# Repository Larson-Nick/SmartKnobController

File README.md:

# Smart Knob Controller

The Smart Knob Controller is an exploration of how brushless DC motors can breathe new life into one of the most ubiquitous input devices—the humble knob—by enabling dynamic, software-configurable feedback. The result is a clean, tactile, dual-degree-of-freedom controller that feels like multiple knobs in one: snappy detents, elastic spring force, or a completely free-spinning dial. The only limit is your creativity.

📘 [View the full Doxygen documentation here](https://larson-nick.github.io/SmartKnobController)

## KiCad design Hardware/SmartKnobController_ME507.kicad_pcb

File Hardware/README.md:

# Hardware

This folder contains all mechanical and electrical design files for the Smart Knob Controller, created using KiCAD v9.0 and SolidWorks 2024.

## Contents

- **Schematics (.sch)** – Complete circuit design
- **PCB Layout (.kicad_pcb)** – Board layout with mounting features
- **CAD** – For mechanical reference and rendering
- **DATASHEETS** - Incomplete list of datasheet PDFs for components
- **LIBRARIES** – Custom components and footprints
- **MANUFACTURING** - All manufacturing files used for production on JLCPCB.com
- **MEDIA** - Images and videos used for the webpage

Open the `.kicad_pro` or `.pro` file in KiCAD 7.0+ to explore the full project.

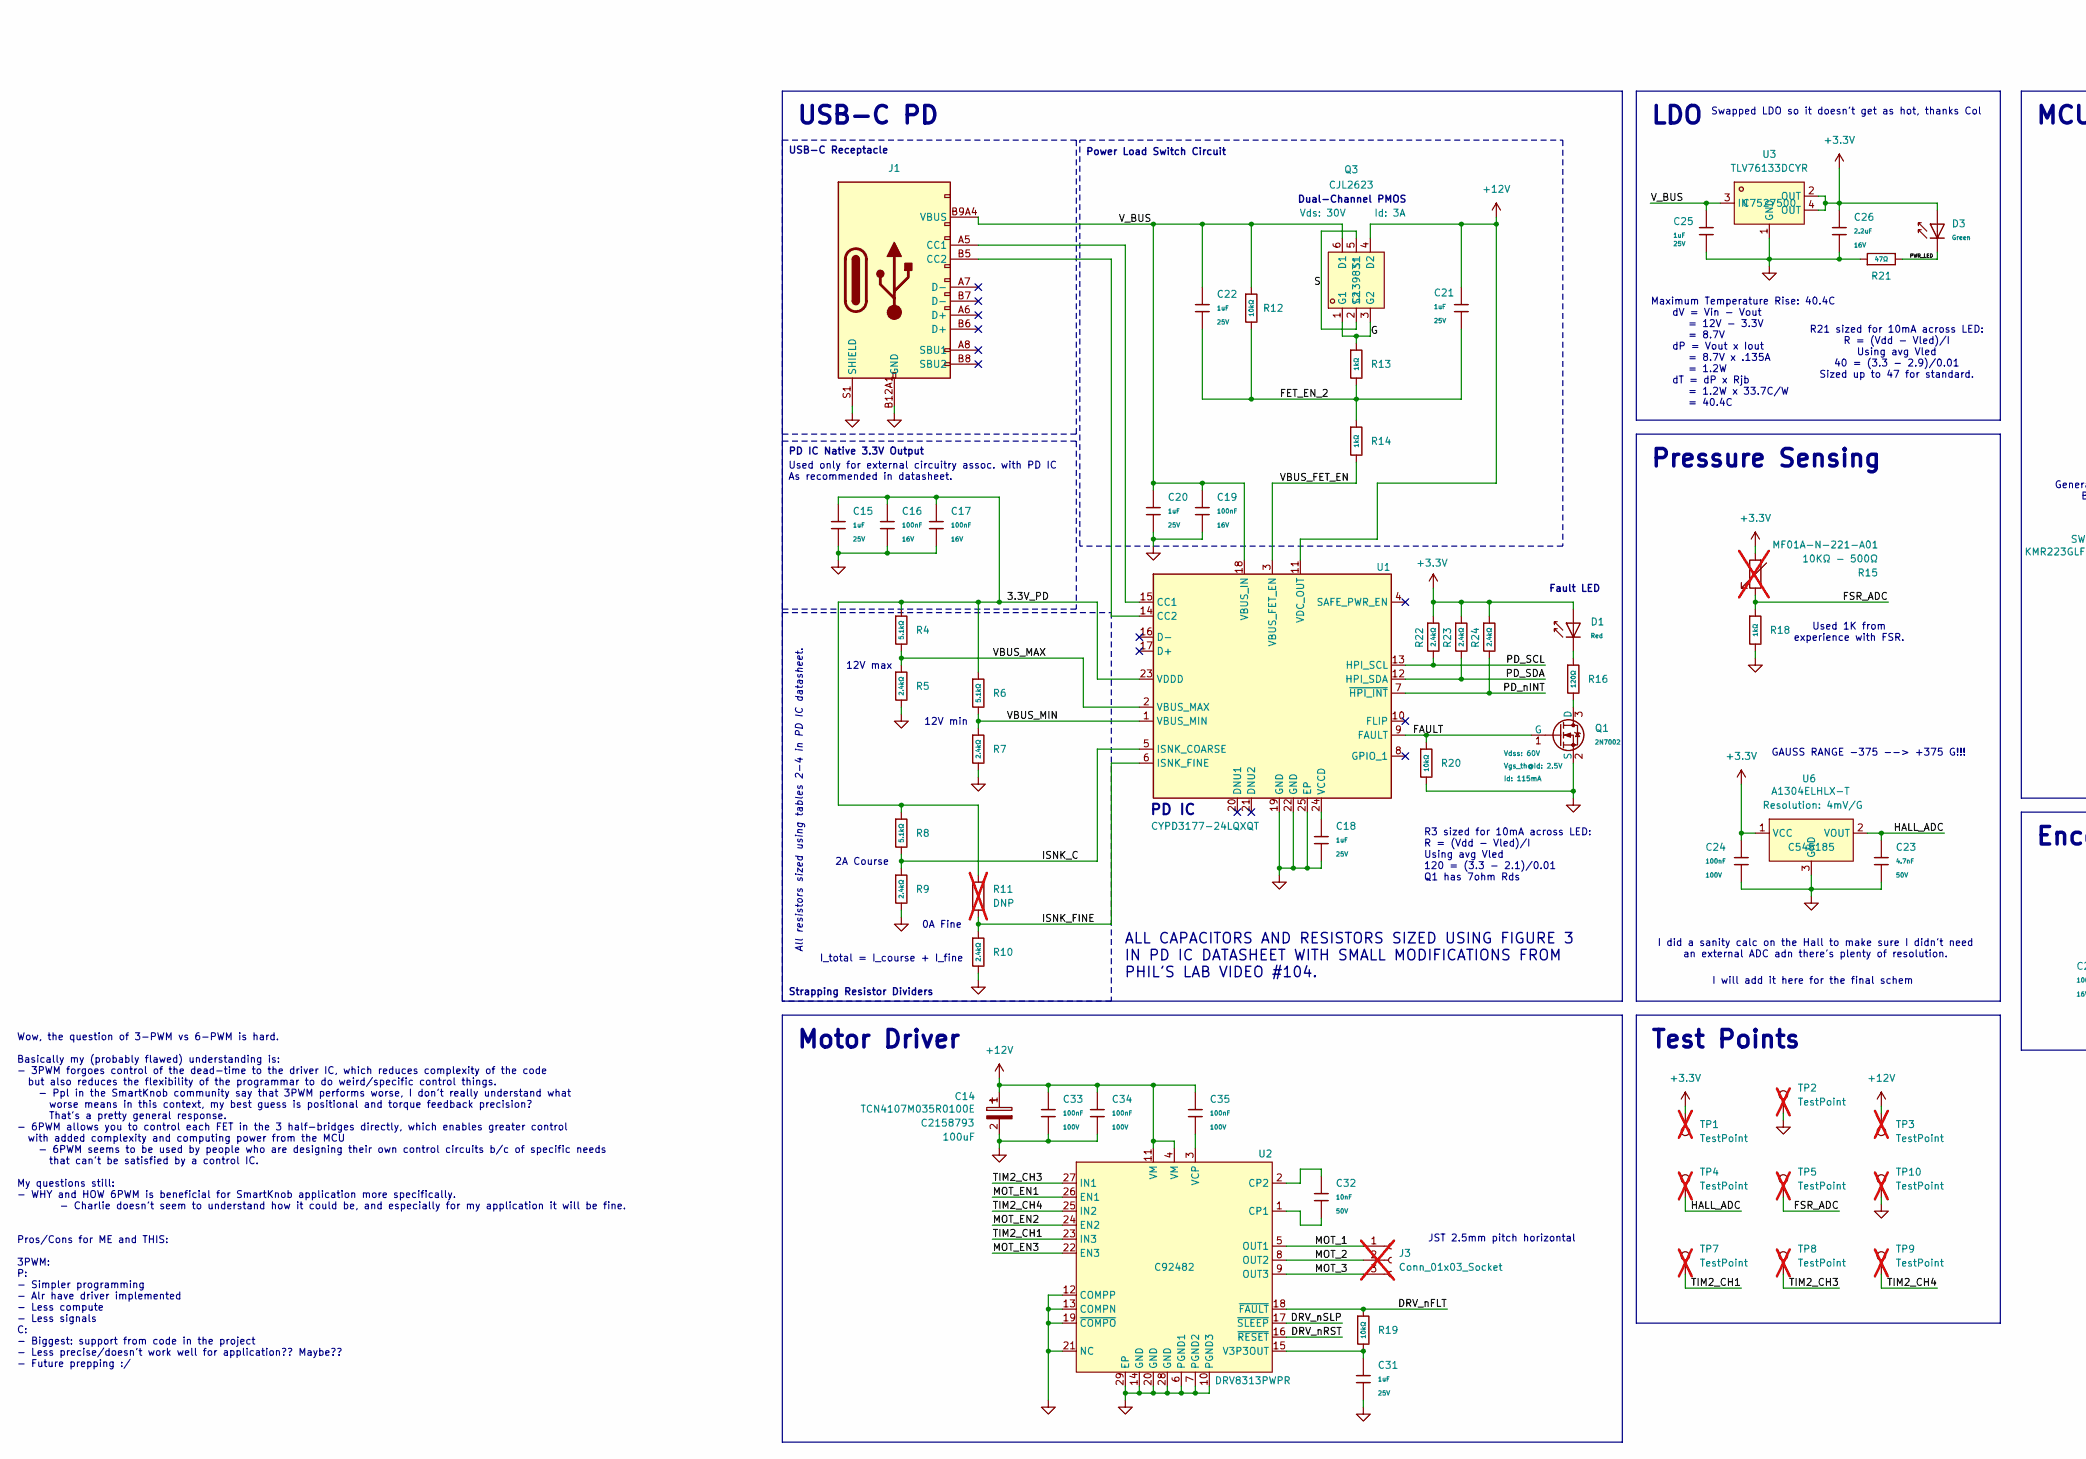
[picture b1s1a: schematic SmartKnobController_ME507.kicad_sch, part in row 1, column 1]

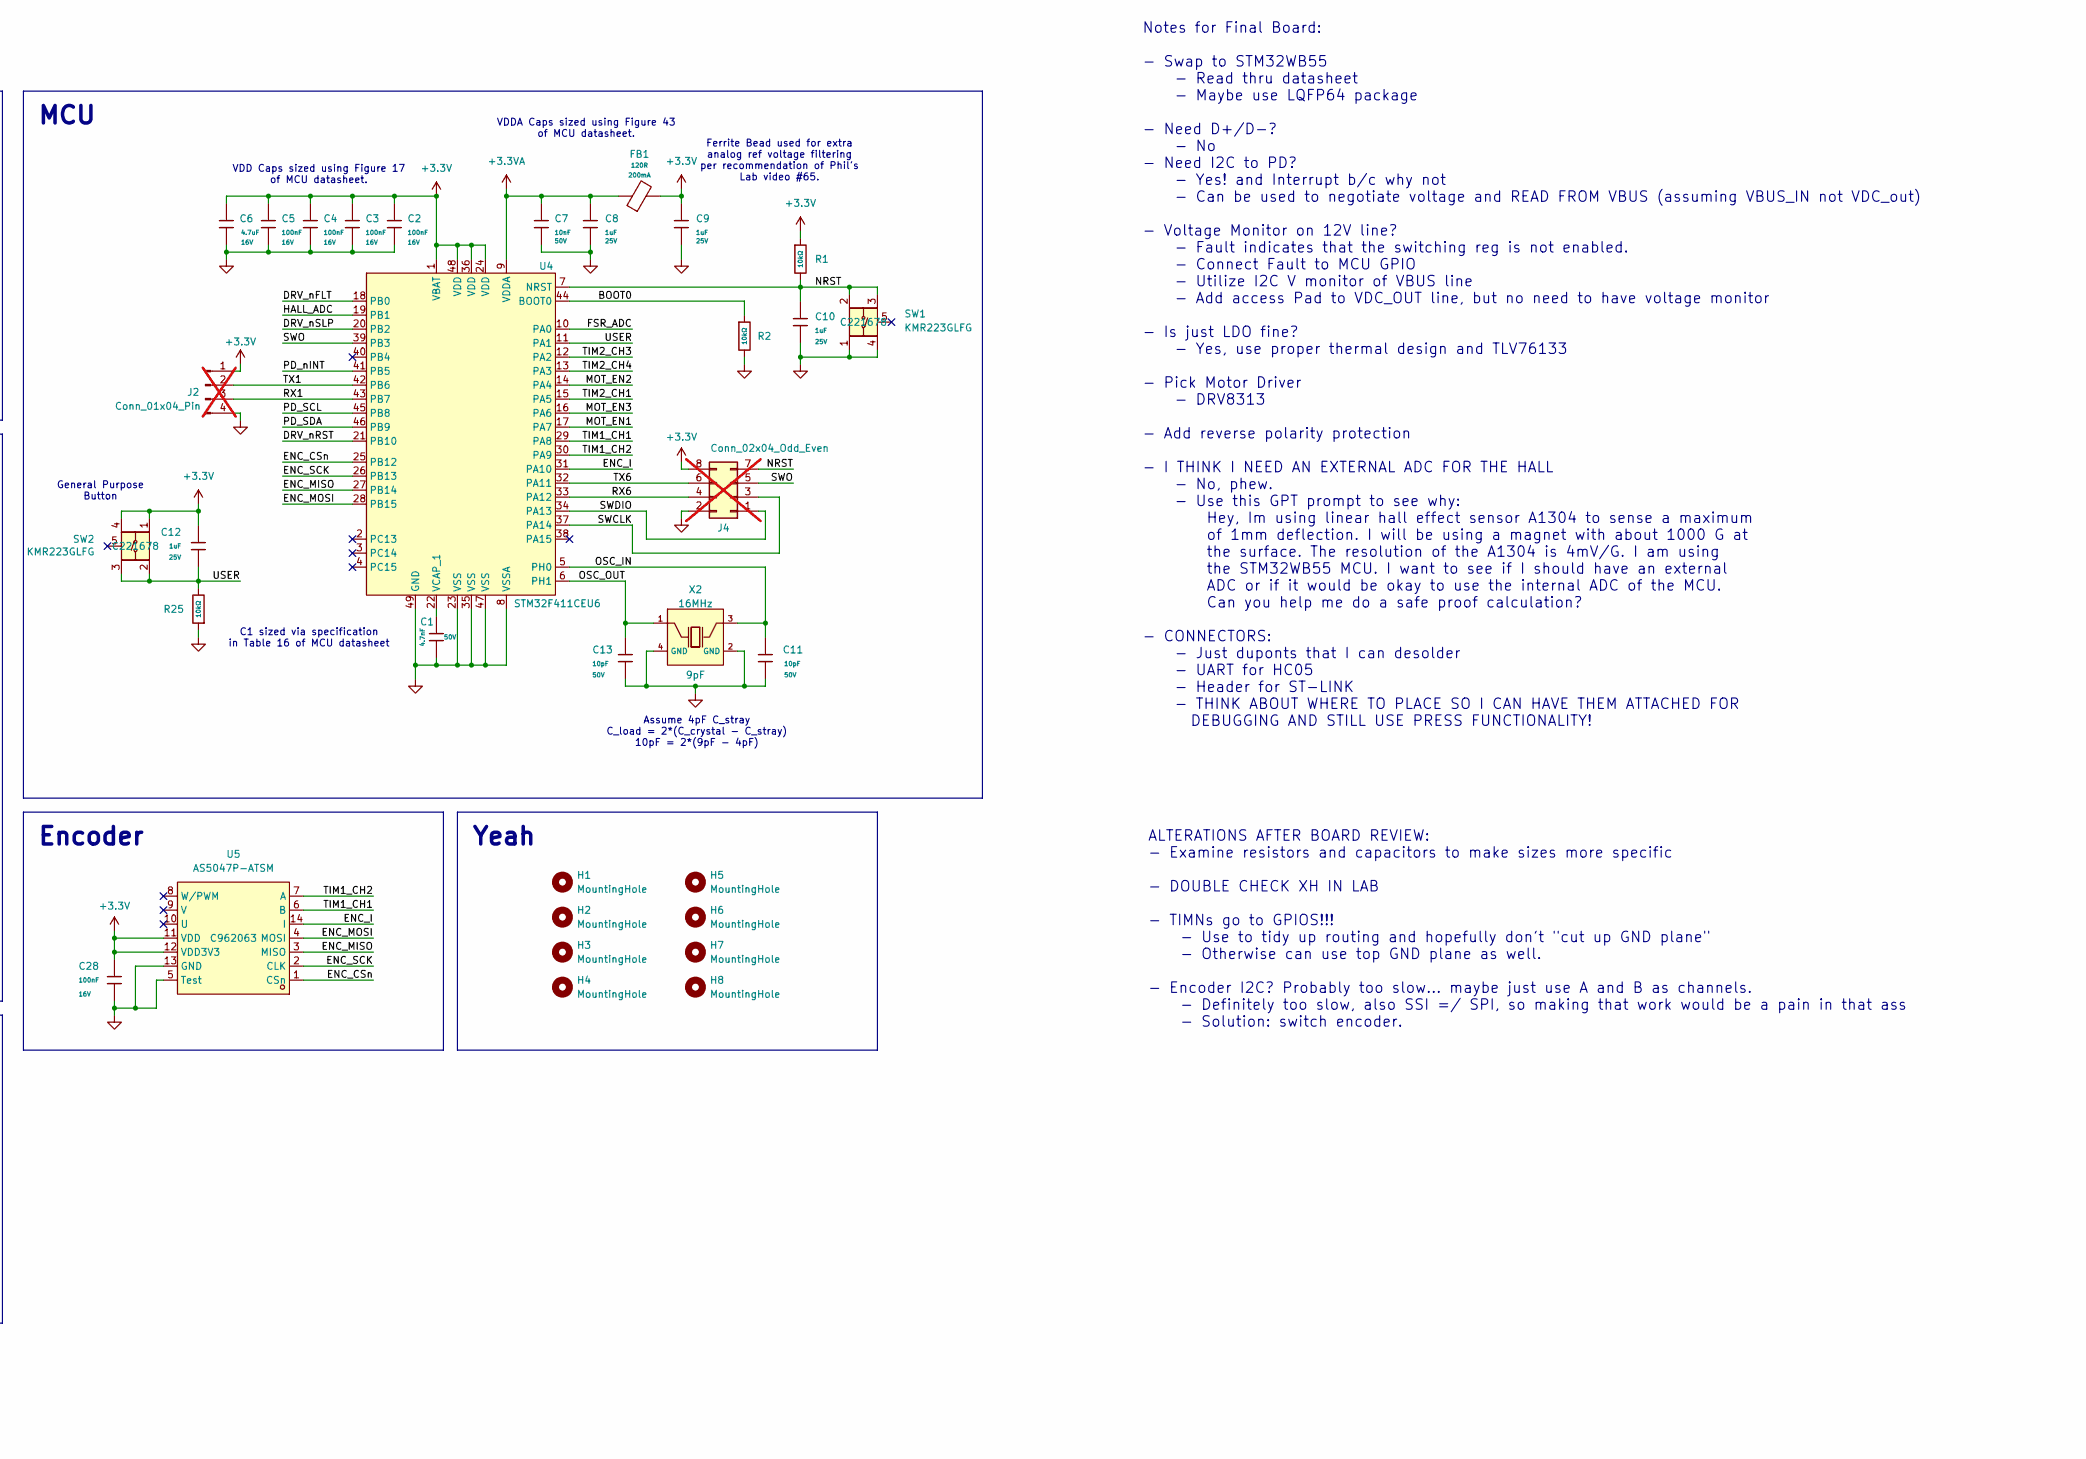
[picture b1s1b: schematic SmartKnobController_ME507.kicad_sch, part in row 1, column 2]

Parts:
C1: 4.7nF; C_0402; Voltage Rated 50V; Tolerance ±10%; Part 0402B472K500NT; LCSC C1538
C2, C3, C4, C5, C16, C17, C19, C28: 100nF; C_0402; Voltage Rated 16V; Tolerance ±10%; Part CL05B104KO5NNNC; LCSC C1525
C6: 4.7uF; C_0603; Voltage Rated 16V; Tolerance ±10%; Part CL10A475KO8NNNC; LCSC C19666
C7, C32: 10nF; C_0402; Voltage Rated 50V; Tolerance ±10%; Part CL05B103KB5NNNC; LCSC C15195
C8, C9, C10, C12, C15, C18, C20, C21, C22, C25, C31: 1uF; C_0402; Voltage Rated 25V; Tolerance ±10%; Part CL05A105KA5NQNC; LCSC C52923
C11, C13: 10pF; C_0402; Voltage Rated 50V; Tolerance ±5%; Part CL05C100JB5NNNC; LCSC C32949
C14: TCN4107M035R0100E; CAP-SMD_L7.3-W6.1_TCN4227M025R0100; LCSC Part C2158793
C23: 4.7nF; C_0805; Voltage Rated 50V; Tolerance ±10%; Part 0805B472K500NT; LCSC C1744
C24, C33, C34, C35: 100nF; C_0805; Voltage Rated 100V; Tolerance ±10%; Part CL21B104KCFNNNE; LCSC C28233
C26: 2.2uF; C_0603; Voltage Rated 16V; Tolerance ±10%; Part CL10A225KO8NNNC; LCSC C23630
D1: Red; D_0603; Part KT-0603R; LCSC C2286
D3: Green; D_0805; Part KT-0805G; LCSC C2297
FB1: 120R; FB_0603; Current Rating 200mA; Tolerance ±25%; Part GZ1608D601TF; LCSC C1002
H1, H2, H3, H4: MountingHole; MountingHole_2.7mm_M2.5
H5, H6, H7, H8: MountingHole; MountingHole_3.2mm_M3
J1: Connector, USB-TYPE-C-16P; TYPE-C-SMD_HX-TYPE-C-16PIN; LCSC C2927039
J2: Conn_01x04_Pin; PinHeader_1x04_P2.54mm_Horizontal; not fitted
J3: Conn_01x03_Socket; JST_XH_S3B-XH-A_1x03_P2.50mm_Horizontal; not fitted
J4: Conn_02x04_Odd_Even; PinHeader_2x04_P2.54mm_Vertical; not fitted
Q1: 2N7002; Q_SOT-23; Part 2N7002; LCSC C8545
Q3: CJL2623; SOT-23-6_L2.9-W1.6-P0.95-LS2.8-BR; LCSC Part C139831
R1, R2, R12, R19, R25: 10kΩ; R_0402; Overload Voltage (Max) 50V; Tolerance ±1%; Part 0402WGF1002TCE; LCSC C25744
R4, R6, R8: 5.1kΩ; R_0603; Overload Voltage (Max) 75V; Tolerance ±1%; Part 0603WAF5101T5E; LCSC C23186
R5, R7, R9, R10: 2.4kΩ; R_0603; Overload Voltage (Max) 75V; Tolerance ±1%; Part 0603WAF2401T5E; LCSC C22940
R11: DNP; R_0603; not fitted
R13, R14: 1kΩ; R_0402; Overload Voltage (Max) 50V; Tolerance ±1%; Part 0402WGF1001TCE; LCSC C11702
R15: 10KΩ - 500Ω; MF01A-N-221-A05; not fitted
R16: 120Ω; R_0603; Overload Voltage (Max) 75V; Tolerance ±1%; Part 0603WAF1200T5E; LCSC C22787
R18: 1kΩ; R_0603; Overload Voltage (Max) 75V; Tolerance ±1%; Part 0603WAF1001T5E; LCSC C21190
R20: 10kΩ; R_0603; Overload Voltage (Max) 75V; Tolerance ±1%; Part 0603WAF1002T5E; LCSC C25804
R21: 47Ω; R_0402; Overload Voltage (Max) 50V; Tolerance ±1%; Part 0402WGF470JTCE; LCSC C25118
R22, R23, R24: 2.4kΩ; R_0402; Overload Voltage (Max) 50V; Tolerance ±1%; Part 0402WGF2401TCE; LCSC C25882
SW1, SW2: KMR223GLFG; SW-SMD_5P-L4.2-W2.8-P1.60-LS4.6-TR; LCSC Part C221678
TP1, TP2, TP3, TP4, TP5, TP7, TP8, TP9, TP10: TestPoint; Test Point; not fitted
U1: CYPD3177-24LQXQT; QFN24_CYPD3177-24LQXQT_INF; LCSC C5904158
U2: DRV8313PWPR; HTSSOP-28_L9.8-W4.5-P0.65-LS6.6-BL-EP; LCSC Part C92482
U3: TLV76133DCYR; SOT-223-4_L6.5-W3.5-P2.30-LS7.0-TR; LCSC Part C7527500
U4: STM32F411CEU6; LCSC C60420
U5: AS5047P-ATSM; TSSOP-14_L5.0-W4.4-P0.65-LS6.4-BL; LCSC Part C962063
U6: A1304ELHLX-T; SOT-23-3_L3.0-W1.9-P0.95-LS2.9-BL; LCSC Part C545185
X2: X322516MLB4SI; OSC-SMD_4P-L3.2-W2.5-BL; Frequency Tolerance ±10ppm; Part X322516MLB4SI; LCSC C13738

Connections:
+3.3V: C2.1, C3.1, C4.1, C5.1, C6.1, C9.1, C12.2, C24.1, C26.1, C28.2, D1.2, D3.2, FB1.2, J2.1, J4.8, R1.1, R15.2, R22.1, R23.1, R24.1, SW2.1, SW2.4, TP1.1, U3.2 (OUT), U3.4 (OUT), U4.1 (VBAT), U4.24 (VDD), U4.36 (VDD), U4.48 (VDD), U5.11 (VDD), U5.12 (VDD3V3), U6.1 (VCC)
+3.3VA: C7.1, C8.1, FB1.1, U4.9 (VDDA)
+12V: C14.1, C21.1, C33.1, C34.1, C35.1, Q3.4 (D2), TP3.1, U1.11 (VDC_OUT), U2.4 (VM), U2.11 (VM)
/3.3V_PD: C15.1, C16.1, C17.1, R4.1, R6.1, R8.1, R11.1, U1.23 (VDDD)
/BOOT0: R2.1, U4.44 (BOOT0)
/DRV_nFLT: R19.1, U2.18 (~FAULT), U4.18 (PB0)
/DRV_nRST: U2.16 (~RESET), U4.21 (PB10)
/DRV_nSLP: U2.17 (~SLEEP), U4.20 (PB2)
/ENC_CSn: U4.25 (PB12), U5.1 (CSn)
/ENC_I: U4.31 (PA10), U5.14 (I)
/ENC_MISO: U4.27 (PB14), U5.3 (MISO)
/ENC_MOSI: U4.28 (PB15), U5.4 (MOSI)
/ENC_SCK: U4.26 (PB13), U5.2 (CLK)
/FAULT: Q1.1 (G), R20.1, U1.9 (FAULT)
/FET_EN_2: C21.2, C22.2, R12.2, R13.2, R14.1
/FSR_ADC: R15.1, R18.1, TP5.1, U4.10 (PA0)
/G: Q3.1 (G1), Q3.3 (G2), R13.1
/HALL_ADC: C23.1, TP4.1, U4.19 (PB1), U6.2 (VOUT)
/ISNK_C: R8.2, R9.1, U1.5 (ISNK_COARSE)
/ISNK_FINE: R10.1, R11.2, U1.6 (ISNK_FINE)
/MOT_1: J3.1, U2.5 (OUT1)
/MOT_2: J3.2, U2.8 (OUT2)
/MOT_3: J3.3, U2.9 (OUT3)
/MOT_EN1: U2.26 (EN1), U4.17 (PA7)
/MOT_EN2: U2.24 (EN2), U4.14 (PA4)
/MOT_EN3: U2.22 (EN3), U4.16 (PA6)
/NRST: C10.1, J4.7, R1.2, SW1.2, SW1.3, U4.7 (NRST)
/OSC_IN: C11.1, U4.5 (PH0), X2.3 (OSC)
/OSC_OUT: C13.1, U4.6 (PH1), X2.1 (OSC)
/PD_SCL: R22.2, U1.13 (HPI_SCL), U4.45 (PB8)
/PD_SDA: R23.2, U1.12 (HPI_SDA), U4.46 (PB9)
/PD_nINT: R24.2, U1.7 (~HPI_INT), U4.41 (PB5)
/PWR_LED: D3.1, R21.2
/RX1: J2.3, U4.43 (PB7)
/RX6: J4.4, U4.33 (PA12)
/S: Q3.2 (S2), Q3.5 (S1)
/SWCLK: J4.3, U4.37 (PA14)
/SWDIO: J4.1, U4.34 (PA13)
/SWO: J4.5, U4.39 (PB3)
/TIM1_CH1: U4.29 (PA8), U5.6 (B)
/TIM1_CH2: U4.30 (PA9), U5.7 (A)
/TIM2_CH1: TP7.1, U2.23 (IN3), U4.15 (PA5)
/TIM2_CH3: TP8.1, U2.27 (IN1), U4.12 (PA2)
/TIM2_CH4: TP9.1, U2.25 (IN2), U4.13 (PA3)
/TX1: J2.2, U4.42 (PB6)
/TX6: J4.6, U4.32 (PA11)
/USER: C12.1, R25.2, SW2.2, SW2.3, U4.11 (PA1)
/VBUS_FET_EN: R14.2, U1.3 (VBUS_FET_EN)
/VBUS_MAX: R4.2, R5.1, U1.2 (VBUS_MAX)
/VBUS_MIN: R6.2, R7.1, U1.1 (VBUS_MIN)
/V_BUS: C19.1, C20.1, C22.1, C25.1, J1.A9B4 (VBUS), J1.B9A4 (VBUS), Q3.6 (D1), R12.1, U1.18 (VBUS_IN), U3.3 (IN)
GND: C1.2, C2.2, C3.2, C4.2, C5.2, C6.2, C7.2, C8.2, C9.2, C10.2, C11.2, C13.2, C14.2, C15.2, C16.2, C17.2, C18.2, C19.2, C20.2, C23.2, C24.2, C25.2, C26.2, C28.1, C31.2, C33.2, C34.2, J1.A12B1 (GND), J1.B12A1 (GND), J1.S1 (SHIELD), J2.4, J4.2, Q1.2 (S), R2.2, R5.2, R7.2, R9.2, R10.2, R18.2, R20.2, R21.1, R25.1, SW1.1, SW1.4, TP2.1, TP10.1, U1.19 (GND), U1.22 (GND), U1.25 (EP), U2.6 (PGND1), U2.7 (PGND2), U2.10 (PGND3), U2.12 (COMPP), U2.13 (COMPN), U2.14 (GND), U2.19 (~COMPO), U2.20 (GND), U2.21 (NC), U2.28 (GND), U2.29 (EP), U3.1 (GND), U4.8 (VSSA), U4.23 (VSS), U4.35 (VSS), U4.47 (VSS), U4.49 (GND), U5.5 (Test), U5.13 (GND), U6.3 (GND), X2.2 (GND), X2.4 (GND)
unnamed: D1.1, R16.1
unnamed: J1.A5 (CC1), U1.15 (CC1)
unnamed: J1.B5 (CC2), U1.14 (CC2)
unnamed: Q1.3 (D), R16.2
unnamed: C18.1, U1.24 (VCCD)
unnamed: C32.2, U2.1 (CP1)
unnamed: C32.1, U2.2 (CP2)
unnamed: C31.1, R19.2, U2.15 (V3P3OUT)
unnamed: C35.2, U2.3 (VCP)
unnamed: C1.1, U4.22 (VCAP_1)

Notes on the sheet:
Dual-Channel PMOS
R3 sized for 10mA across LED: R = (Vdd - Vled)/I Using avg Vled 120 = (3.3 - 2.1)/0.01 Q1 has 7ohm Rds
Used only for external circuitry assoc. with PD IC As recommended in datasheet.
Used 1K from experience with FSR.
Fault LED
Maximum Temperature Rise: 40.4C dV = Vin - Vout = 12V - 3.3V = 8.7V dP = Vout x Iout = 8.7V x .135A = 1.2W dT = dP x Rjb = 1.2W x 33.7C/W = 40.4C
VDDA Caps sized using Figure 43 of MCU datasheet.
R21 sized for 10mA across LED: R = (Vdd - Vled)/I Using avg Vled 40 = (3.3 - 2.9)/0.01 Sized up to 47 for standard.
12V min
2A Course
C1 sized via specification in Table 16 of MCU datasheet
GAUSS RANGE -375 --> +375 G!!!
0A Fine
ALTERATIONS AFTER BOARD REVIEW: - Examine resistors and capacitors to make sizes more specific - DOUBLE CHECK XH IN LAB - TIMNs go to GPIOS!!! - Use to tidy up routing and hopefully don't "cut up GND plane" - Otherwise can use top GND plane as well. - Encoder I2C? Probably too slow... maybe just us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
PD IC
VDD Caps sized using Figure 17 of MCU datasheet.
Power Load Switch Circuit
General Purpose Button
JST 2.5mm pitch horizontal
I did a sanity calc on the Hall to make sure I didn't need an external ADC adn there's plenty of resolution.
Notes for Final Board: - Swap to STM32WB55 - Read thru datasheet - Maybe use LQFP64 package - Need D+/D-? - No - Need I2C to PD? - Yes! and Interrupt b/c why not - Can be used to negotiate voltage and READ FROM VBUS (assuming VBUS_IN not VDC_out) - Voltage Monitor on 12V line? - Fault indicates tha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
Swapped LDO so it doesn't get as hot, thanks Col
Wow, the question of 3-PWM vs 6-PWM is hard. Basically my (probably flawed) understanding is: - 3PWM forgoes control of the dead-time to the driver IC, which reduces complexity of the code but also reduces the flexibility of the programmar to do weird/specific control things. - Ppl in the SmartKnob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
Assume 4pF C_stray C_load = 2*(C_crystal - C_stray) 10pF = 2*(9pF - 4pF)
I will add it here for the final schem
I_total = I_course + I_fine
12V max
All resistors sized using tables 2-4 in PD IC datasheet.
ALL CAPACITORS AND RESISTORS SIZED USING FIGURE 3 IN PD IC DATASHEET WITH SMALL MODIFICATIONS FROM PHIL'S LAB VIDEO #104.
Ferrite Bead used for extra analog ref voltage filtering per recommendation of Phil's Lab video #65.
Motor Driver
LDO
Pressure Sensing
Encoder
PD IC Native 3.3V Output
Strapping Resistor Dividers
Test Points
Yeah
USB-C Receptacle
USB-C PD

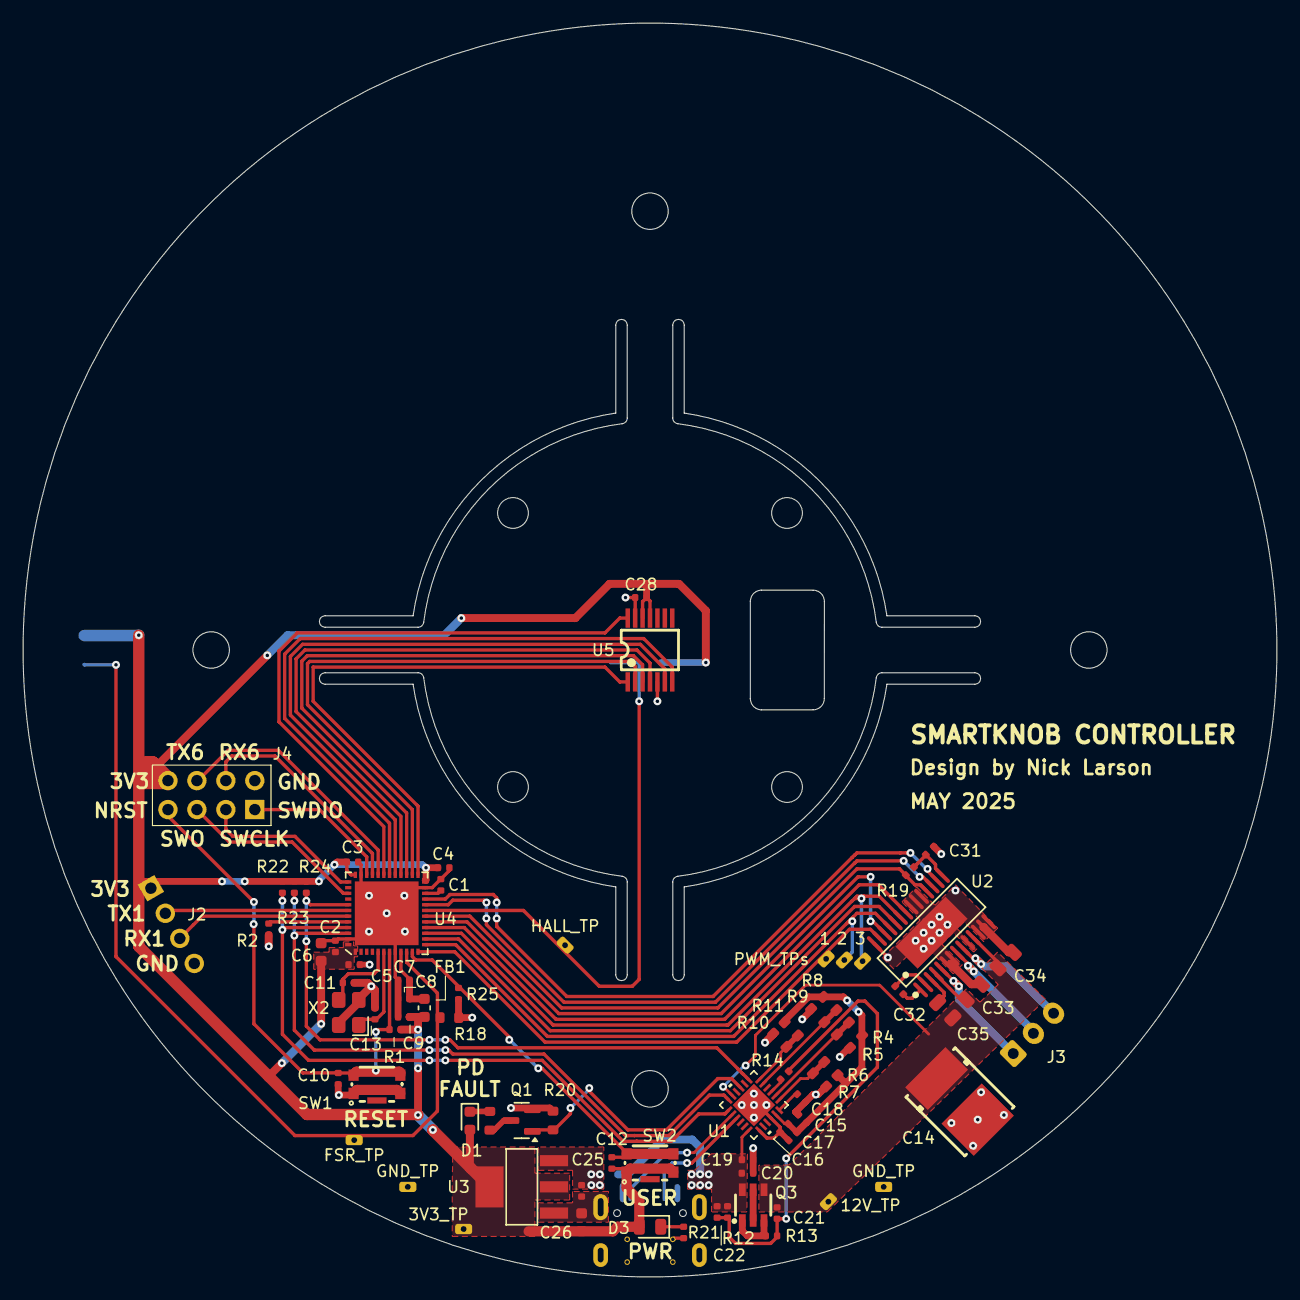
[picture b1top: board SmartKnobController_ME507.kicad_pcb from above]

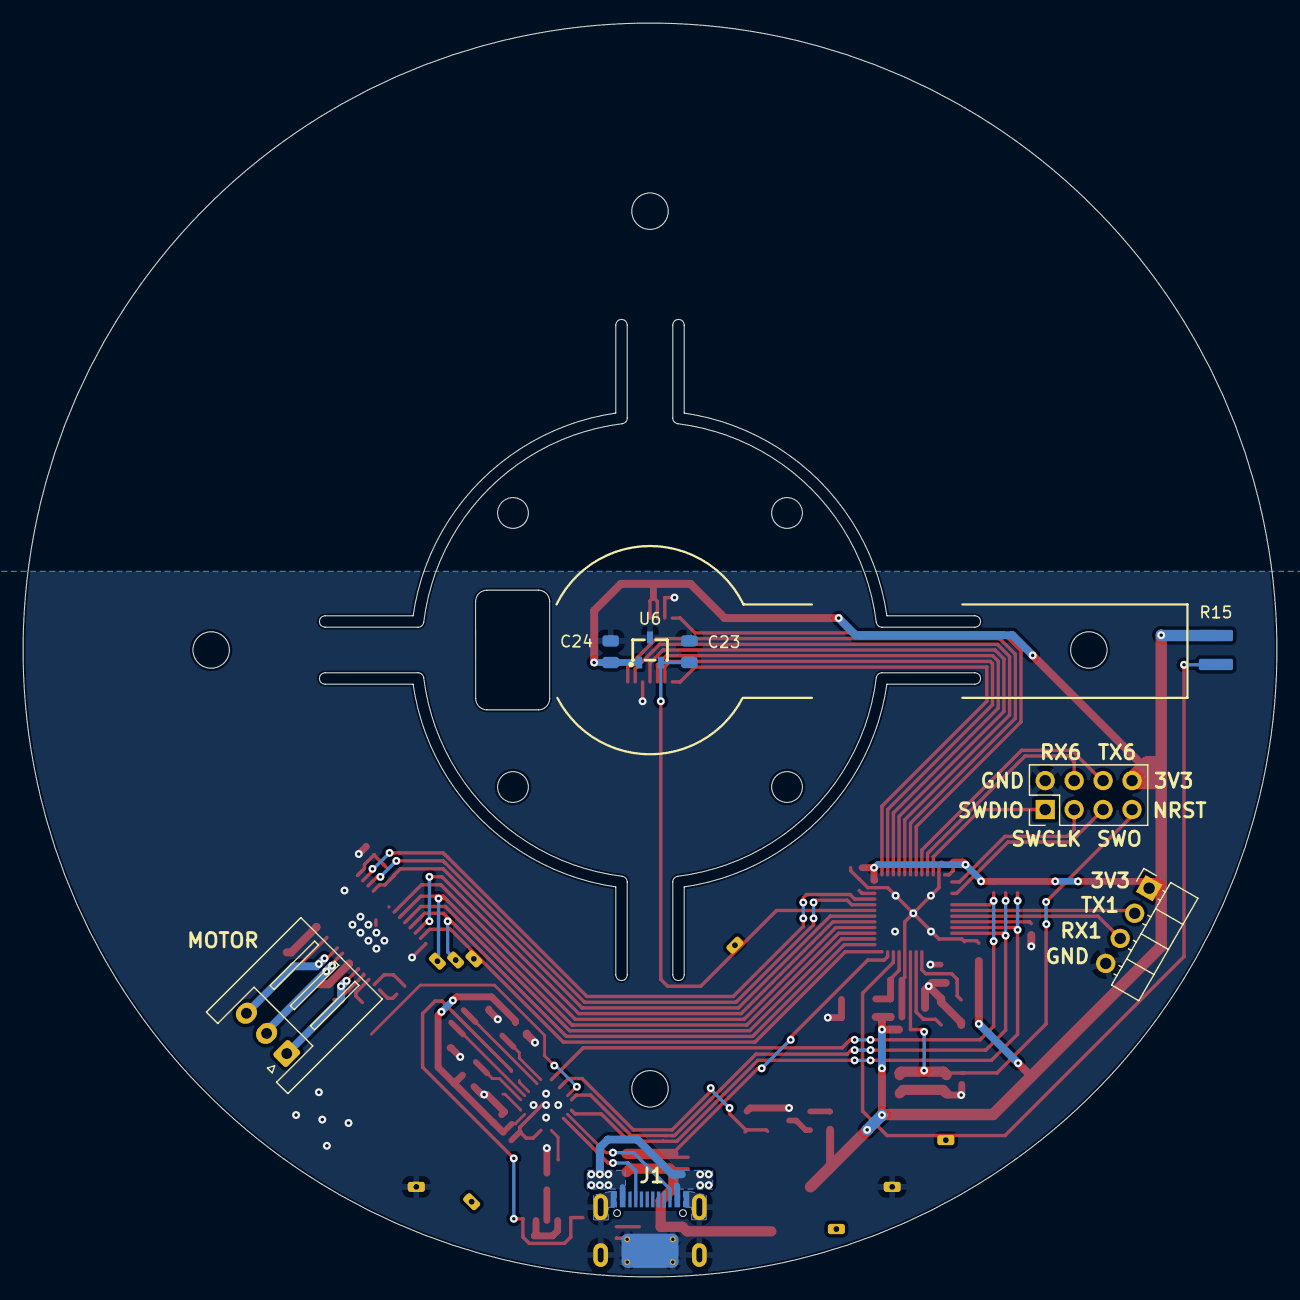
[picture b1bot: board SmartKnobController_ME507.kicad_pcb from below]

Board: 2 copper layers, 110.0 x 110.0 mm, 90 parts (8 on the bottom side), 62 nets.

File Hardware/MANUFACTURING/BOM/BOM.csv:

"Reference","Value","Footprint","Description","Qty","LCSC","DNP"
"Q3","CJL2623","0_TRANSISTOR:SOT-23-6_L2.9-W1.6-P0.95-LS2.8-BR","","1","C139831",""
"U5","AS5047P-ATSM","0_SENSOR:TSSOP-14_L5.0-W4.4-P0.65-LS6.4-BL","","1","C962063",""
"D1","Red","PCM_JLCPCB:D_0603","-40°C~+85°C Red 0603 LED Indication - Discrete ROHS","1","C2286",""
"R20","10kΩ","PCM_JLCPCB:R_0603","100mW Thick Film Resistors 75V ±100ppm/°C ±1% 10kΩ 0603 Chip Resistor - Surface Mount ROHS","1","C25804",""
"R16","120Ω","PCM_JLCPCB:R_0603","100mW Thick Film Resistors 75V ±100ppm/°C ±1% 120Ω 0603 Chip Resistor - Surface Mount ROHS","1","C22787",""
"R18","1kΩ","PCM_JLCPCB:R_0603","100mW Thick Film Resistors 75V ±100ppm/°C ±1% 1kΩ 0603 Chip Resistor - Surface Mount ROHS","1","C21190",""
"R5,R7,R9,R10","2.4kΩ","PCM_JLCPCB:R_0603","100mW Thick Film Resistors 75V ±100ppm/°C ±1% 2.4kΩ 0603 Chip Resistor - Surface Mount ROHS","4","C22940",""
"R4,R6,R8","5.1kΩ","PCM_JLCPCB:R_0603","100mW Thick Film Resistors 75V ±100ppm/°C ±1% 5.1kΩ 0603 Chip Resistor - Surface Mount ROHS","3","C23186",""
"C14","TCN4107M035R0100E","0_CAPACITOR:CAP-SMD_L7.3-W6.1_TCN4227M025R0100","100uF 35V 100mΩ@100kHz ±20% Tantalum Capacitors ROHS","1","C2158793",""
"C24,C33,C34,C35","100nF","PCM_JLCPCB:C_0805","100V 100nF X7R ±10% 0805 Multilayer Ceramic Capacitors MLCC - SMD/SMT ROHS","4","C28233",""
"X2","X322516MLB4SI","PCM_JLCPCB:OSC-SMD_4P-L3.2-W2.5-BL","16MHz Surface Mount Crystal 9pF ±10ppm ±20ppm SMD3225-4P Crystals ROHS","1","C13738",""
"C2,C3,C4,C5,C16,C17,C19,C28","100nF","PCM_JLCPCB:C_0402","16V 100nF X7R ±10% 0402 Multilayer Ceramic Capacitors MLCC - SMD/SMT ROHS","8","C1525",""
"C26","2.2uF","PCM_JLCPCB:C_0603","16V 2.2uF X5R ±10% 0603 Multilayer Ceramic Capacitors MLCC - SMD/SMT ROHS","1","C23630",""
"C6","4.7uF","PCM_JLCPCB:C_0603","16V 4.7uF X5R ±10% 0603 Multilayer Ceramic Capacitors MLCC - SMD/SMT ROHS","1","C19666",""
"U3","TLV76133DCYR","0_PWR:SOT-223-4_L6.5-W3.5-P2.30-LS7.0-TR","1A Fixed 3.3V Positive electrode 16V SOT-223 Voltage Regulators - Linear, Low Drop Out (LDO) Regulators ROHS","1","C7527500",""
"C8,C9,C10,C12,C15,C18,C20,C21,C22,C25,C31","1uF","PCM_JLCPCB:C_0402","25V 1uF X5R ±10% 0402 Multilayer Ceramic Capacitors MLCC - SMD/SMT ROHS","11","C52923",""
"J1","Connector, USB-TYPE-C-16P","PCM_JLCPCB:TYPE-C-SMD_HX-TYPE-C-16PIN","3A 1 Horizontal attachment 16P Female -25℃~+85℃ Type-C SMD USB Connectors ROHS","1","C2927039",""
"FB1","120R","PCM_JLCPCB:FB_0603","450mΩ ±25% 600Ω@100MHz 0603 Ferrite Beads ROHS","1","C1002",""
"C7,C32","10nF","PCM_JLCPCB:C_0402","50V 10nF X7R ±10% 0402 Multilayer Ceramic Capacitors MLCC - SMD/SMT ROHS","2","C15195",""
"C11,C13","10pF","PCM_JLCPCB:C_0402","50V 10pF C0G ±5% 0402 Multilayer Ceramic Capacitors MLCC - SMD/SMT ROHS","2","C32949",""
"C1","4.7nF","PCM_JLCPCB:C_0402","50V 4.7nF X7R ±10% 0402 Multilayer Ceramic Capacitors MLCC - SMD/SMT ROHS","1","C1538",""
"C23","4.7nF","PCM_JLCPCB:C_0805","50V 4.7nF X7R ±10% 0805 Multilayer Ceramic Capacitors MLCC - SMD/SMT ROHS","1","C1744",""
"Q1","2N7002","PCM_JLCPCB:Q_SOT-23","60V 115mA 200mW 7.5Ω@10V,500mA 2.5V@250uA 1 N-Channel SOT-23 MOSFETs ROHS","1","C8545",""
"R21","47Ω","PCM_JLCPCB:R_0402","62.5mW Thick Film Resistors 50V ±1% ±200ppm/°C 47Ω 0402 Chip Resistor - Surface Mount ROHS","1","C25118",""
"R1,R2,R12,R19,R25","10kΩ","PCM_JLCPCB:R_0402","62.5mW Thick Film Resistors 50V ±100ppm/°C ±1% 10kΩ 0402 Chip Resistor - Surface Mount ROHS","5","C25744",""
"R13,R14","1kΩ","PCM_JLCPCB:R_0402","62.5mW Thick Film Resistors 50V ±100ppm/°C ±1% 1kΩ 0402 Chip Resistor - Surface Mount ROHS","2","C11702",""
"R22,R23,R24","2.4kΩ","PCM_JLCPCB:R_0402","62.5mW Thick Film Resistors 50V ±100ppm/°C ±1% 2.4kΩ 0402 Chip Resistor - Surface Mount ROHS","3","C25882",""
"U4","STM32F411CEU6","0_MCU:STM32F411CEU6","ARM-M4 100MHz UFQFPN-48(7x7) Microcontrollers (MCU/MPU/SOC) ROHS","1","C60420",""
"D3","Green","PCM_JLCPCB:D_0805","Emerald 0805 LED Indication - Discrete ROHS","1","C2297",""
"U2","DRV8313PWPR","0_DRIVER:HTSSOP-28_L9.8-W4.5-P0.65-LS6.6-BL-EP","HTSSOP-28-EP-4.5mm Brushless DC (BLDC) Motor Driver ROHS","1","C92482",""
"SW1,SW2","KMR223GLFG","0_MISC:SW-SMD_5P-L4.2-W2.8-P1.60-LS4.6-TR","Round Button 10mA Standing paste SPST - normally open 32V 200gf SMD Tactile Switches ROHS","2","C221678",""
"U6","A1304ELHLX-T","0_SENSOR:SOT-23-3_L3.0-W1.9-P0.95-LS2.9-BL","SOT-23W Linear Hall Sensors ROHS","1","C545185",""
"U1","CYPD3177-24LQXQT","0_PWR:QFN24_CYPD3177-24LQXQT_INF","Stand-alone USB PD controller (with sink Auto-run mode), QFN-24","1","C5904158",""

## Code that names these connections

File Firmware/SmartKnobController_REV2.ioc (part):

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Mcu.Name=STM32F411C(C-E)Ux
Mcu.Package=UFQFPN48
Mcu.UserName=STM32F411CEUx
PA1.GPIOParameters=GPIO_ModeDefaultEXTI
PA1.GPIO_ModeDefaultEXTI=GPIO_MODE_IT_RISING_FALLING
PA1.Signal=GPXTI1
PA11.Mode=Asynchronous
PA11.Signal=USART6_TX
PA12.Mode=Asynchronous
PA12.Signal=USART6_RX
PA13.Mode=Trace_Asynchronous_SW
PA13.Signal=SYS_JTMS-SWDIO
PA14.Mode=Trace_Asynchronous_SW
PA14.Signal=SYS_JTCK-SWCLK
PA2.Signal=S_TIM2_CH3
PA3.Signal=S_TIM2_CH4
PA4.GPIOParameters=PinState
PA4.PinState=GPIO_PIN_RESET
PA4.Signal=GPIO_Output
PA5.Signal=S_TIM2_CH1_ETR
PA6.GPIOParameters=PinState
PA6.PinState=GPIO_PIN_RESET
PA6.Signal=GPIO_Output
PA7.GPIOParameters=PinState
PA7.PinState=GPIO_PIN_RESET
PA7.Signal=GPIO_Output
PB1.Signal=ADCx_IN9
PB10.GPIOParameters=PinState
PB10.PinState=GPIO_PIN_SET
PB10.Signal=GPIO_Output
PB12.Signal=GPIO_Output
PB13.Mode=Full_Duplex_Master
PB13.Signal=SPI2_SCK
PB14.Mode=Full_Duplex_Master
PB14.Signal=SPI2_MISO
PB15.Mode=Full_Duplex_Master
PB15.Signal=SPI2_MOSI
PB2.GPIOParameters=PinState
PB2.PinState=GPIO_PIN_SET
PB2.Signal=GPIO_Output
PB3.Mode=Trace_Asynchronous_SW
PB3.Signal=SYS_JTDO-SWO
PB6.Mode=Asynchronous
PB6.Signal=USART1_TX
PB7.Mode=Asynchronous
PB7.Signal=USART1_RX
PH0\ -\ OSC_IN.Mode=HSE-External-Oscillator
PH0\ -\ OSC_IN.Signal=RCC_OSC_IN
PH1\ -\ OSC_OUT.Mode=HSE-External-Oscillator
PH1\ -\ OSC_OUT.Signal=RCC_OSC_OUT
RCC.HSE_VALUE=16000000
RCC.SYSCLKFreq_VALUE=72000000
RCC.SYSCLKSource=RCC_SYSCLKSOURCE_PLLCLK
board=custom

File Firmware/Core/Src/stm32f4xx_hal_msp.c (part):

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void HAL_MspInit(void)
{

  /* USER CODE BEGIN MspInit 0 */

  /* USER CODE END MspInit 0 */

  __HAL_RCC_SYSCFG_CLK_ENABLE();
  __HAL_RCC_PWR_CLK_ENABLE();

  /* System interrupt init*/

  /* USER CODE BEGIN MspInit 1 */

  /* USER CODE END MspInit 1 */
}

/**
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  GPIO_InitTypeDef GPIO_InitStruct = {0};
  if(hadc->Instance==ADC1)
  {
    /* USER CODE BEGIN ADC1_MspInit 0 */

    /* USER CODE END ADC1_MspInit 0 */
    /* Peripheral clock enable */
    __HAL_RCC_ADC1_CLK_ENABLE();

    __HAL_RCC_GPIOB_CLK_ENABLE();
    /**ADC1 GPIO Configuration
    PB1     ------> ADC1_IN9
    */
    GPIO_InitStruct.Pin = GPIO_PIN_1;
    GPIO_InitStruct.Mode = GPIO_MODE_ANALOG;
    GPIO_InitStruct.Pull = GPIO_NOPULL;
    HAL_GPIO_Init(GPIOB, &GPIO_InitStruct);

    /* USER CODE BEGIN ADC1_MspInit 1 */

    /* USER CODE END ADC1_MspInit 1 */

  }

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    __HAL_RCC_ADC1_CLK_DISABLE();

    /**ADC1 GPIO Configuration
    PB1     ------> ADC1_IN9
    */
    HAL_GPIO_DeInit(GPIOB, GPIO_PIN_1);

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  GPIO_InitTypeDef GPIO_InitStruct = {0};
  if(hspi->Instance==SPI2)
  {
    /* USER CODE BEGIN SPI2_MspInit 0 */

    /* USER CODE END SPI2_MspInit 0 */
    /* Peripheral clock enable */
    __HAL_RCC_SPI2_CLK_ENABLE();

    __HAL_RCC_GPIOB_CLK_ENABLE();
    /**SPI2 GPIO Configuration
    PB13     ------> SPI2_SCK
    PB14     ------> SPI2_MISO
    PB15     ------> SPI2_MOSI
    */
    GPIO_InitStruct.Pin = GPIO_PIN_13|GPIO_PIN_14|GPIO_PIN_15;
    GPIO_InitStruct.Mode = GPIO_MODE_AF_PP;
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    GPIO_InitStruct.Alternate = GPIO_AF5_SPI2;
    HAL_GPIO_Init(GPIOB, &GPIO_InitStruct);

    /* USER CODE BEGIN SPI2_MspInit 1 */

    /* USER CODE END SPI2_MspInit 1 */

  }

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    __HAL_RCC_SPI2_CLK_DISABLE();

    /**SPI2 GPIO Configuration
    PB13     ------> SPI2_SCK
    PB14     ------> SPI2_MISO
    PB15     ------> SPI2_MOSI
    */
    HAL_GPIO_DeInit(GPIOB, GPIO_PIN_13|GPIO_PIN_14|GPIO_PIN_15);

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{
  if(htim_pwm->Instance==TIM2)
  {
    /* USER CODE BEGIN TIM2_MspInit 0 */

    /* USER CODE END TIM2_MspInit 0 */
    /* Peripheral clock enable */
    __HAL_RCC_TIM2_CLK_ENABLE();
    /* TIM2 interrupt Init */
    HAL_NVIC_SetPriority(TIM2_IRQn, 1, 0);
    HAL_NVIC_EnableIRQ(TIM2_IRQn);
    /* USER CODE BEGIN TIM2_MspInit 1 */

    /* USER CODE END TIM2_MspInit 1 */

  }

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{
  if(htim_base->Instance==TIM4)
  {
    /* USER CODE BEGIN TIM4_MspInit 0 */

    /* USER CODE END TIM4_MspInit 0 */
    /* Peripheral clock enable */
    __HAL_RCC_TIM4_CLK_ENABLE();
    /* USER CODE BEGIN TIM4_MspInit 1 */

    /* USER CODE END TIM4_MspInit 1 */
  }
  else if(htim_base->Instance==TIM5)
  {
    /* USER CODE BEGIN TIM5_MspInit 0 */

    /* USER CODE END TIM5_MspInit 0 */
    /* Peripheral clock enable */
    __HAL_RCC_TIM5_CLK_ENABLE();
    /* USER CODE BEGIN TIM5_MspInit 1 */

    /* USER CODE END TIM5_MspInit 1 */
  }

}
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
    __HAL_RCC_GPIOA_CLK_ENABLE();
    /**TIM2 GPIO Configuration
    PA2     ------> TIM2_CH3
    PA3     ------> TIM2_CH4
    PA5     ------> TIM2_CH1
    */
    GPIO_InitStruct.Pin = GPIO_PIN_2|GPIO_PIN_3|GPIO_PIN_5;
    GPIO_InitStruct.Mode = GPIO_MODE_AF_PP;
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  GPIO_InitTypeDef GPIO_InitStruct = {0};
  if(huart->Instance==USART1)
  {
    /* USER CODE BEGIN USART1_MspInit 0 */

    /* USER CODE END USART1_MspInit 0 */
    /* Peripheral clock enable */
    __HAL_RCC_USART1_CLK_ENABLE();

    __HAL_RCC_GPIOB_CLK_ENABLE();
    /**USART1 GPIO Configuration
    PB6     ------> USART1_TX
    PB7     ------> USART1_RX
    */
    GPIO_InitStruct.Pin = GPIO_PIN_6|GPIO_PIN_7;
    GPIO_InitStruct.Mode = GPIO_MODE_AF_PP;
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    GPIO_InitStruct.Alternate = GPIO_AF7_USART1;
    HAL_GPIO_Init(GPIOB, &GPIO_InitStruct);

    /* USER CODE BEGIN USART1_MspInit 1 */

    /* USER CODE END USART1_MspInit 1 */
  }
  else if(huart->Instance==USART6)
  {
    /* USER CODE BEGIN USART6_MspInit 0 */

    /* USER CODE END USART6_MspInit 0 */
    /* Peripheral clock enable */
    __HAL_RCC_USART6_CLK_ENABLE();

    __HAL_RCC_GPIOA_CLK_ENABLE();
    /**USART6 GPIO Configuration
    PA11     ------> USART6_TX
    PA12     ------> USART6_RX
    */
    GPIO_InitStruct.Pin = GPIO_PIN_11|GPIO_PIN_12;
    GPIO_InitStruct.Mode = GPIO_MODE_AF_PP;
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    GPIO_InitStruct.Alternate = GPIO_AF8_USART6;
    HAL_GPIO_Init(GPIOA, &GPIO_InitStruct);

    /* USER CODE BEGIN USART6_MspInit 1 */

    /* USER CODE END USART6_MspInit 1 */
  }

}
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    __HAL_RCC_USART1_CLK_DISABLE();

    /**USART1 GPIO Configuration
    PB6     ------> USART1_TX
    PB7     ------> USART1_RX
    */
    HAL_GPIO_DeInit(GPIOB, GPIO_PIN_6|GPIO_PIN_7);

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    __HAL_RCC_USART6_CLK_DISABLE();

    /**USART6 GPIO Configuration
    PA11     ------> USART6_TX
    PA12     ------> USART6_RX
    */
    HAL_GPIO_DeInit(GPIOA, GPIO_PIN_11|GPIO_PIN_12);

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
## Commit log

2025-06-14 Added Doxygen documentation and README
2025-06-14 Updated .gitignore to ignore build and temp files
2025-06-14 Added project contents
2025-06-14 Updated Repo README

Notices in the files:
Firmware/Core/Src/stm32f4xx_hal_msp.c:
Copyright (c) 2025 STMicroelectronics.
All rights reserved.
This software is licensed under terms that can be found in the LICENSE file
